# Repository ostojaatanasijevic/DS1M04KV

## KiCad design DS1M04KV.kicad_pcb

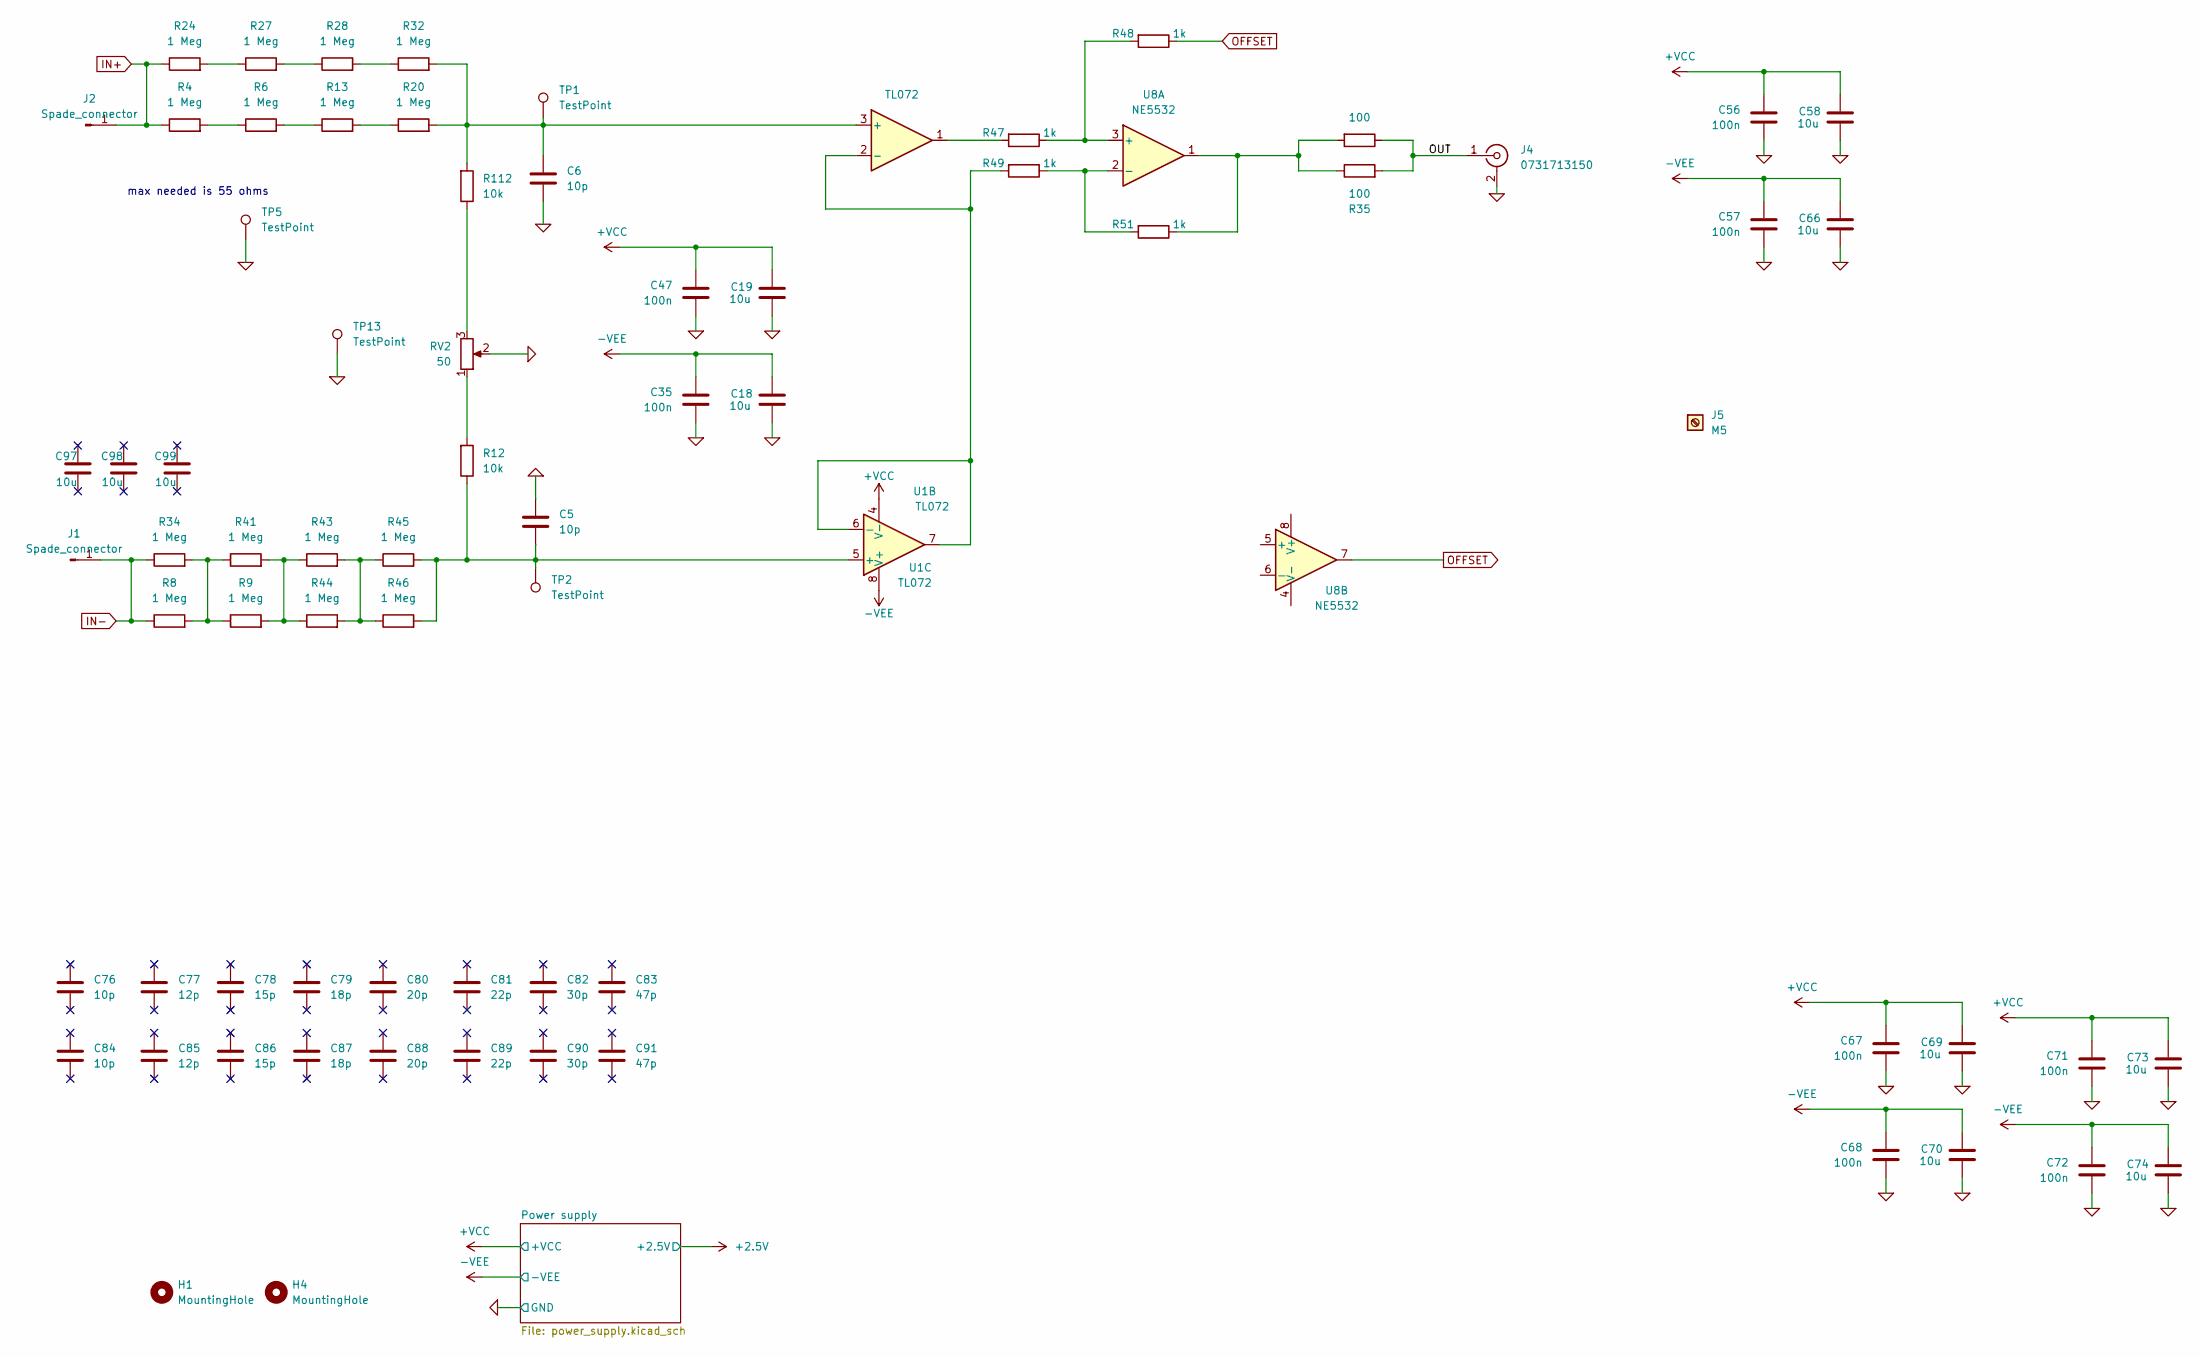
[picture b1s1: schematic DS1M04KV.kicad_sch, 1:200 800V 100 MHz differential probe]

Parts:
C5, C6, C76, C84: 10p; R_0603_1608Metric_Pad0.98x0.95mm_HandSolder; LCSC C1634
C18, C19, C58, C66, C69, C70, C73, C74: 10u; C_0603_1608Metric_Pad1.08x0.95mm_HandSolder; LCSC C96446
C35, C47, C56, C57, C67, C68, C71, C72: 100n; C_0603_1608Metric_Pad1.08x0.95mm_HandSolder; LCSC C14663
C77, C85: 12p; R_0603_1608Metric_Pad0.98x0.95mm_HandSolder; LCSC C38523
C78, C86: 15p; R_0603_1608Metric_Pad0.98x0.95mm_HandSolder; LCSC C1644
C79, C87: 18p; R_0603_1608Metric_Pad0.98x0.95mm_HandSolder; LCSC C1644
C80, C88: 20p; R_0603_1608Metric_Pad0.98x0.95mm_HandSolder; LCSC C1648
C81, C89: 22p; R_0603_1608Metric_Pad0.98x0.95mm_HandSolder; LCSC C1653
C82, C90: 30p; R_0603_1608Metric_Pad0.98x0.95mm_HandSolder; LCSC C1658
C83, C91: 47p; R_0603_1608Metric_Pad0.98x0.95mm_HandSolder; LCSC C1648
C97, C98, C99: 10u; R_0805_2012Metric_Pad1.20x1.40mm_HandSolder; Voltage 25V; LCSC C15850
H1, H4: MountingHole; M3_with_screw
J1, J2: Spade_connector; spade_connector_mid_PCB
J4: 0731713150; 0731000105
J5: M5; M5_floating
R4, R6, R8, R9, R13, R20, R24, R27, R28, R32, R34, R41, R43, R44, R45, R46: 1 Meg; R_1206_3216Metric_Pad1.30x1.75mm_HandSolder; LCSC C17927
R12, R112: 10k; R_0603_1608Metric_Pad0.98x0.95mm_HandSolder; LCSC C25804
R17, R35: 100; R_0603_1608Metric_Pad0.98x0.95mm_HandSolder; LCSC C22775
R47, R48, R49, R51: 1k; R_0603_1608Metric_Pad0.98x0.95mm_HandSolder; LCSC C21190
RV2: 50; Potentiometer_Bourns_3296W_Vertical
TP1, TP2, TP5, TP13: TestPoint; TestPoint_Pad_D2.0mm
U1: TL072; SOIC-8_3.9x4.9mm_P1.27mm; LCSC C6961
U8: NE5532; SOIC-8_3.9x4.9mm_P1.27mm

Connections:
0: C5.2, C6.1, C18.2, C19.2, C35.1, C47.1, C56.1, C57.1, C58.2, C66.2, C67.1, C68.1, C69.2, C70.2, C71.1, C72.1, C73.2, C74.2, J4.2 (Ext), RV2.2, TP5.1 (1_1), TP13.1 (1_1); also elsewhere on the board
+VCC: C19.1, C47.2, C56.2, C58.1, C67.2, C69.1, C71.2, C73.1, U1.4 (V-); also elsewhere on the board
-VEE: C18.1, C35.2, C57.2, C66.1, C68.2, C70.1, C72.2, C74.1, U1.8 (V+); also elsewhere on the board
/OUT: J4.1 (In), R17.1, R35.2
IN+: J2.1 (Pin_1_1), R4.1, R24.1
IN-: J1.1 (Pin_1_1), R8.1, R34.1
unnamed: R4.2, R6.1
unnamed: R12.2, RV2.1
unnamed: R6.2, R13.1
unnamed: R13.2, R20.1
unnamed: R17.2, R35.1, R51.1, U8.1
unnamed: R24.2, R27.1
unnamed: R27.2, R28.1
unnamed: R28.2, R32.1
unnamed: R8.2, R9.1, R34.2, R41.1
unnamed: R9.2, R41.2, R43.1, R44.1
unnamed: R43.2, R44.2, R45.1, R46.1
unnamed: R47.2, U1.1
unnamed: R112.1, RV2.3
unnamed: C6.2, R20.2, R32.2, R112.2, TP1.1 (1_1), U1.3 (+)
unnamed: R49.2, U1.2 (-), U1.6 (-), U1.7
unnamed: C5.1, R12.1, R45.2, R46.2, TP2.1 (1_1), U1.5 (+)
unnamed: R47.1, R48.2, U8.3 (+)
unnamed: R49.1, R51.2, U8.2 (-)
OFFSET: R48.1, U8.7

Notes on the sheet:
max needed is 55 ohms

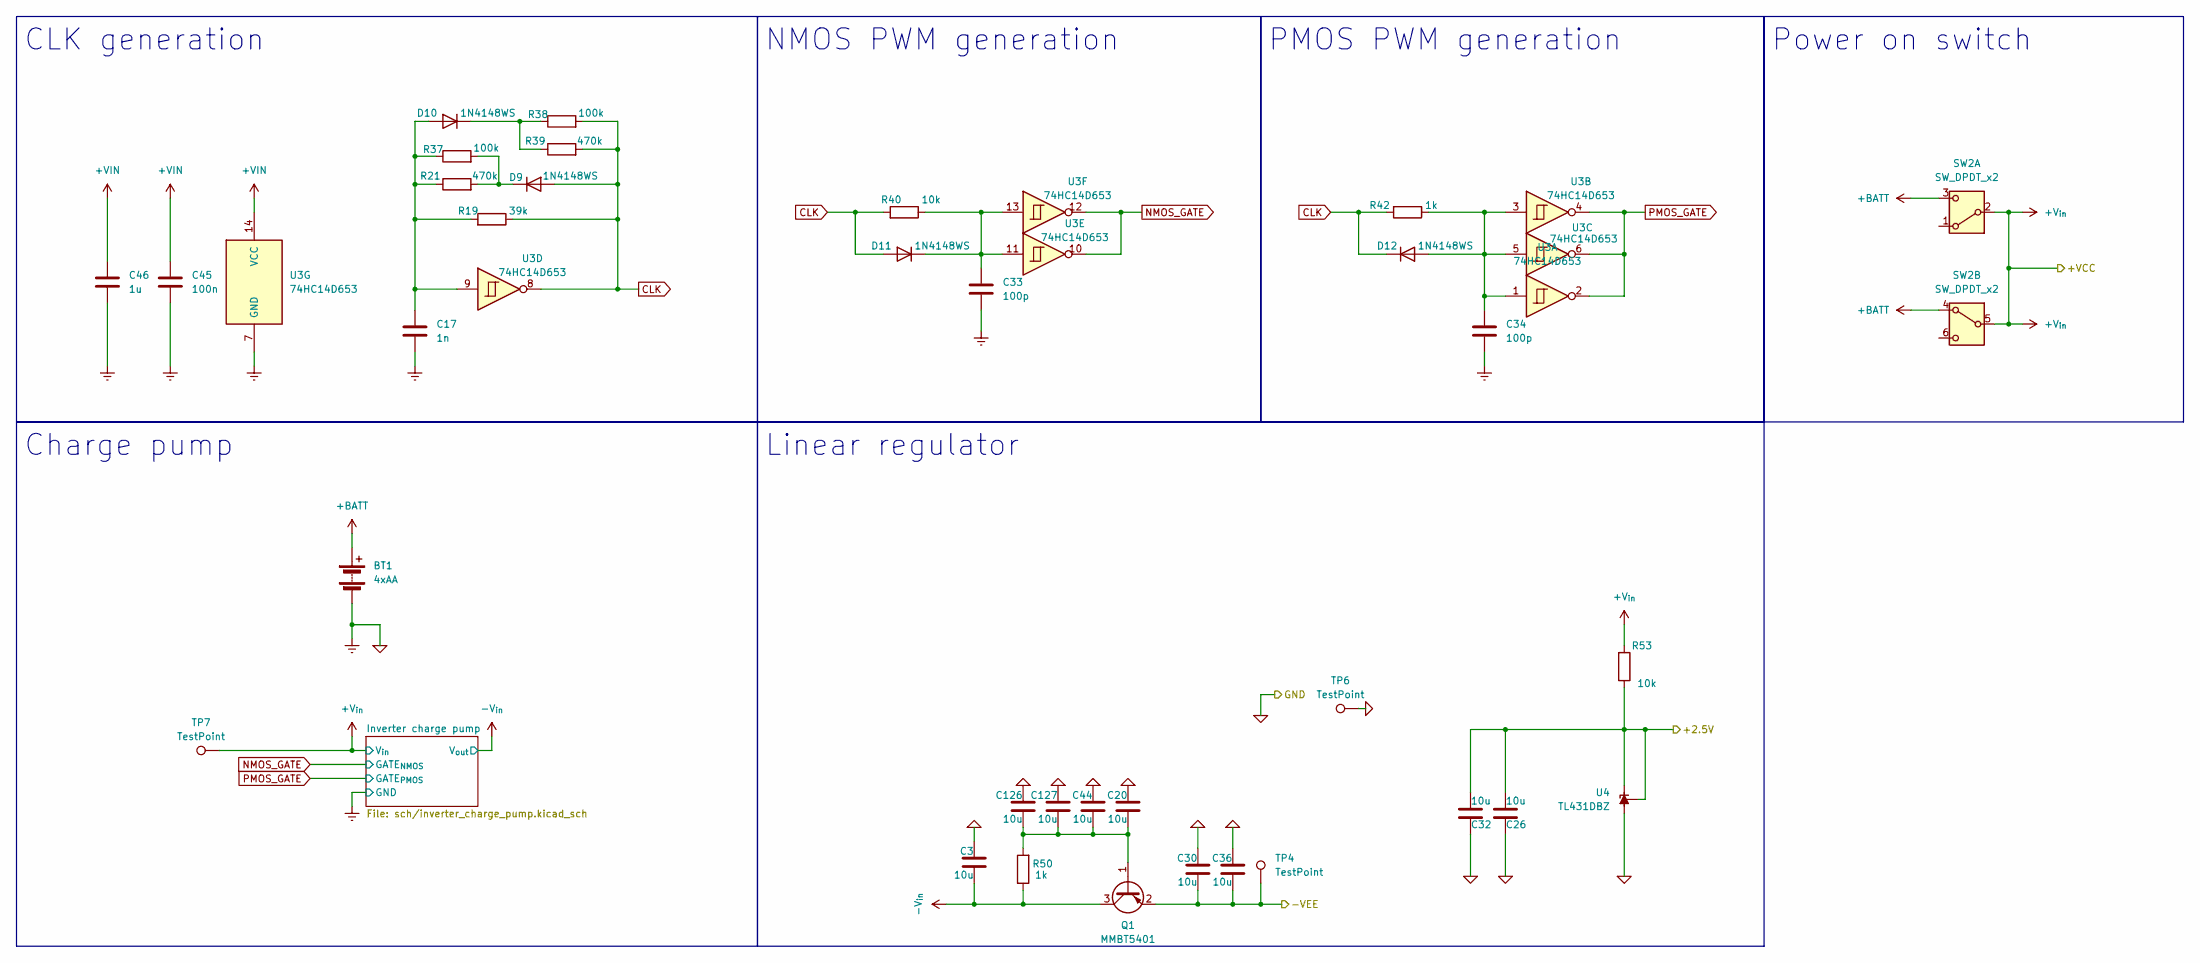
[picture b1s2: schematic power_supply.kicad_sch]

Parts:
BT1: 4xAA; BatteryHolder_MPD_BC2AAPC_2xAA
C3, C20, C26, C30, C32, C36, C44, C126, C127: 10u; R_0805_2012Metric_Pad1.20x1.40mm_HandSolder; Voltage 25V; LCSC C15850
C17: 1n; C_0603_1608Metric_Pad1.08x0.95mm_HandSolder; LCSC C1588
C33, C34: 100p; C_0603_1608Metric_Pad1.08x0.95mm_HandSolder; LCSC C14858
C45: 100n; C_0603_1608Metric_Pad1.08x0.95mm_HandSolder; LCSC C14663
C46: 1u; C_0603_1608Metric_Pad1.08x0.95mm_HandSolder; LCSC C15849
D9, D10, D11, D12: 1N4148WS; D_SOD-323; LCSC C2128
Q1: MMBT5401; SOT-23; LCSC C8326
R19: 39k; R_0603_1608Metric_Pad0.98x0.95mm_HandSolder; LCSC C23153
R21, R39: 470k; R_0603_1608Metric_Pad0.98x0.95mm_HandSolder; LCSC C23178
R37, R38: 100k; R_0603_1608Metric_Pad0.98x0.95mm_HandSolder; LCSC C25803
R40, R53: 10k; R_0603_1608Metric_Pad0.98x0.95mm_HandSolder; LCSC C25804
R42, R50: 1k; R_0603_1608Metric_Pad0.98x0.95mm_HandSolder; LCSC C21190
SW2: SW_DPDT_x2; DPDT_bigger
TP4, TP6, TP7: TestPoint; TestPoint_Pad_D2.0mm
U3: 74HC14D653; SOIC-14_3.9x8.7mm_P1.27mm; LCSC C5605
U4: TL431DBZ; SOT-23; LCSC C3113

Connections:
0: BT1.2 (-), C3.2, C17.1, C20.2, C26.2, C30.2, C32.2, C33.1, C34.1, C36.2, C44.2, C45.1, C46.1, C126.2, C127.2, TP6.1 (1_1), U3.7 (GND), U4.3 (A); also elsewhere on the board
+2.5V: C26.1, C32.1, R53.1, U4.1 (K), U4.2 (REF)
+BATT: BT1.1 (+), SW2.3 (C), SW2.4 (A)
+VCC: R53.2, SW2.2 (B), SW2.5 (B), TP7.1 (1_1); also elsewhere on the board
+VIN: C45.2, C46.2, U3.14 (VCC); also elsewhere on the board
-VEE: C30.1, C36.1, Q1.2 (E), TP4.1 (1_1); also elsewhere on the board
-V_{in}: C3.1, Q1.3 (C), R50.1; also elsewhere on the board
CLK: D9.2 (A), D11.2 (A), D12.1 (K), R19.1, R38.2, R39.2, R40.2, R42.2, U3.8
NMOS_GATE: U3.10, U3.12; also elsewhere on the board
unnamed: D9.1 (K), R21.2, R37.2
unnamed: C17.2, D10.2 (A), R19.2, R21.1, R37.1, U3.9
unnamed: D10.1 (K), R38.1, R39.1
unnamed: C33.2, D11.1 (K), R40.1, U3.11, U3.13
unnamed: C34.2, D12.2 (A), R42.1, U3.1, U3.3, U3.5
unnamed: C20.1, C44.1, C126.1, C127.1, Q1.1 (B), R50.2
PMOS_GATE: U3.2, U3.4, U3.6; also elsewhere on the board

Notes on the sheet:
Charge pump
CLK generation
Power on switch
Linear regulator
PMOS PWM generation
NMOS PWM generation

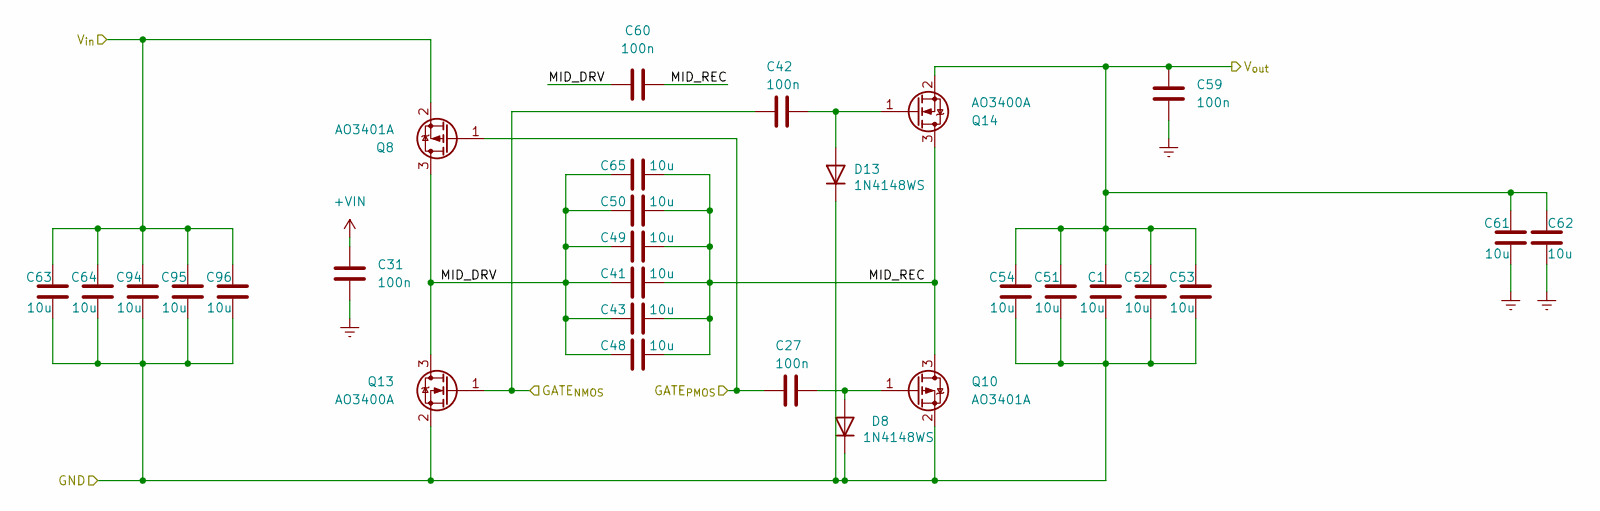
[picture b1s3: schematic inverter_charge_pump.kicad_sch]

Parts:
C1, C41, C43, C48, C49, C50, C51, C52, C53, C54, C61, C62, C63, C64, C65, C94, C95, C96: 10u; R_0805_2012Metric_Pad1.20x1.40mm_HandSolder; Voltage 25V; LCSC C15850
C27, C31, C42, C59, C60: 100n; C_0603_1608Metric_Pad1.08x0.95mm_HandSolder; LCSC C14663
D8, D13: 1N4148WS; D_SOD-323; LCSC C2128
Q8, Q10: AO3401A; SOT-23; LCSC C15127
Q13, Q14: AO3400A; SOT-23; LCSC C20917

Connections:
0: C1.1, C31.1, C51.1, C52.1, C53.1, C54.1, C59.1, C61.1, C62.1, C63.1, C64.1, C94.1, C95.1, C96.1, D8.1 (K), D13.1 (K), Q10.2 (S), Q13.2 (S); also elsewhere on the board
+VCC: C63.2, C64.2, C94.2, C95.2, C96.2, Q8.2 (S); also elsewhere on the board
+VIN: C31.2; also elsewhere on the board
-V_{in}: C1.2, C51.2, C52.2, C53.2, C54.2, C59.2, C61.2, C62.2, Q14.2 (S); also elsewhere on the board
/Power supply/Inverter charge pump/MID_DRV: C41.1, C43.1, C48.1, C49.1, C50.1, C60.2, C65.1, Q8.3 (D), Q13.3 (D)
/Power supply/Inverter charge pump/MID_REC: C41.2, C43.2, C48.2, C49.2, C50.2, C60.1, C65.2, Q10.3 (D), Q14.3 (D)
NMOS_GATE: C42.1, Q13.1 (G); also elsewhere on the board
unnamed: C27.2, D8.2 (A), Q10.1 (G)
unnamed: C42.2, D13.2 (A), Q14.1 (G)
PMOS_GATE: C27.1, Q8.1 (G); also elsewhere on the board

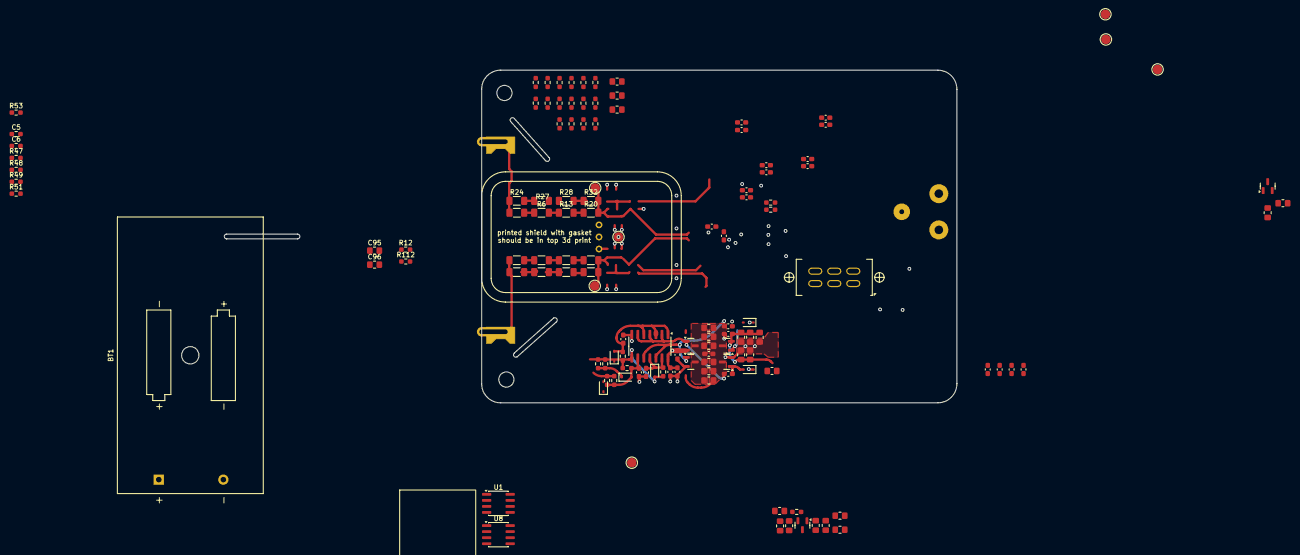
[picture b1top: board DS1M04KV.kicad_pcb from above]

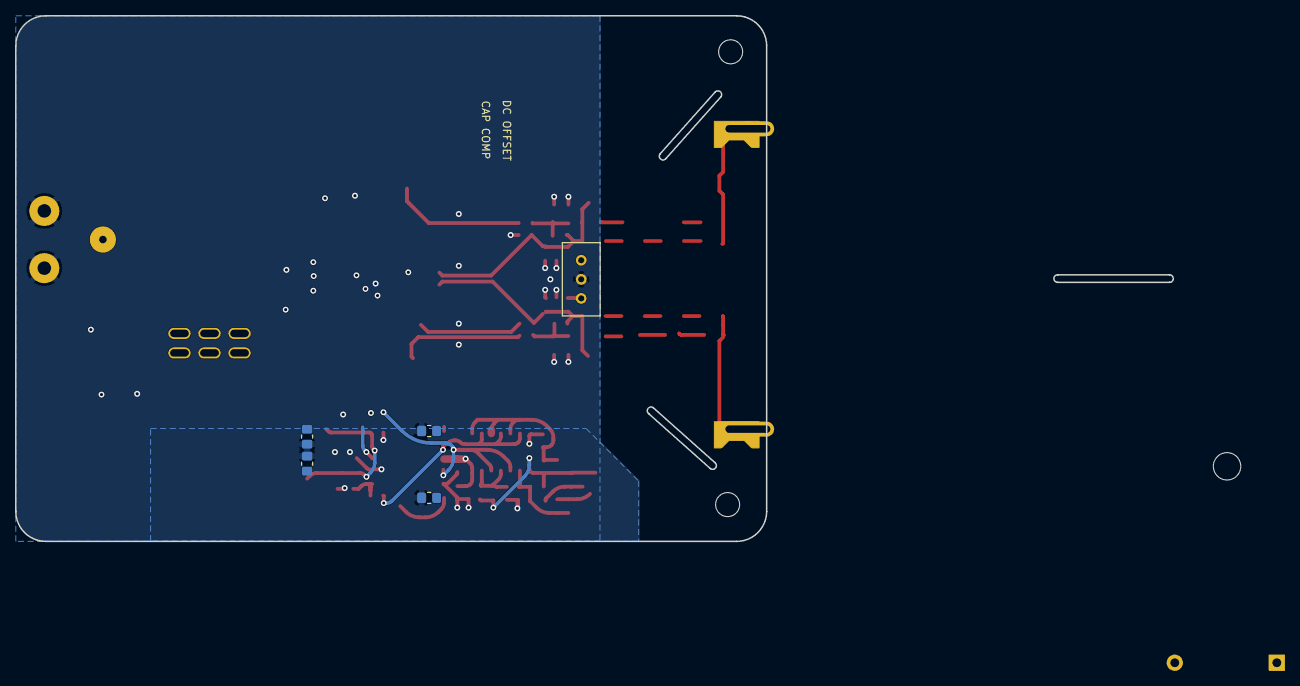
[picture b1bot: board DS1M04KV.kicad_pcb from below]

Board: 2 copper layers, 138 parts (10 on the bottom side), 42 nets.
